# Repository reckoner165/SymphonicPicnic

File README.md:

# SymphonicPicnic
A repo for Teensy and XBee codes for the mushrooms

TEsting : Arduino Teensy Changes for SD optimization
enable : #define USE_TEENSY3_OPTIMIZED_CODE
SD_t3.h : /Applications/<Arduino-App-Folder>/Contents/Java/hardware/teensy/avr/libraries/SD/SD_t3.h

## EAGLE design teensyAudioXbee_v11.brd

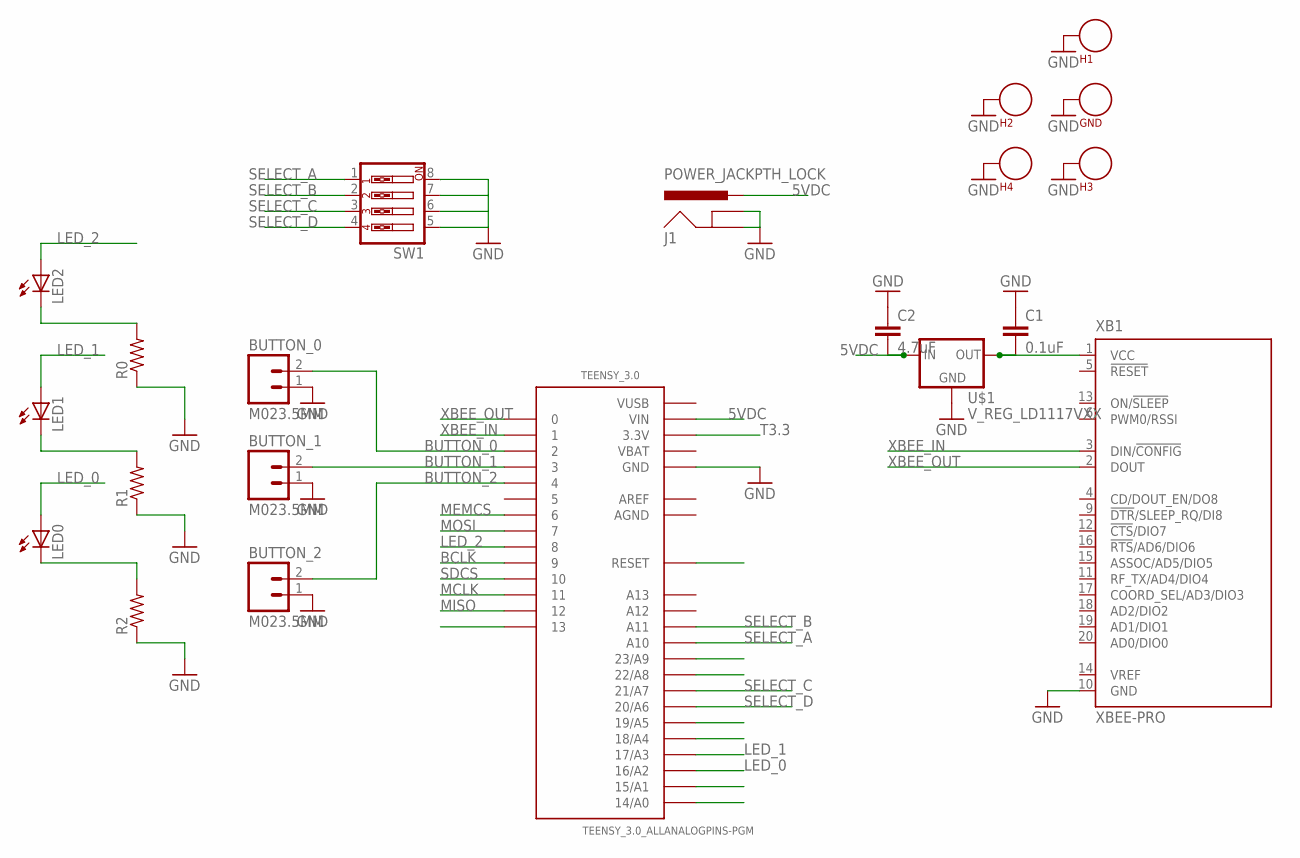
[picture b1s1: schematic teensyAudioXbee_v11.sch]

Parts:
BUTTON_0, BUTTON_1, BUTTON_2: M023.5MM; SCREWTERMINAL-3.5MM-2
C1: 0.1uF; CAP-PTH-SMALLEZ
C2: 4.7uF; CAP-PTH-SMALLEZ
GND: SEW_HOLE; SIMPLE_HOLE
H1, H2, H3, H4: SEW_HOLE; SIMPLE_HOLE
J1: POWER_JACKPTH_LOCK; POWER_JACK_PTH_LOCK
LED0, LED1, LED2: LED_ELD260; LED_LD260
R0, R1, R2: RESISTORPTH-1/6W; 1/6W-RES
SW1: SW_DIP-4; EDG-04
TEENSY_3.0: TEENSY_3.0_ALLANALOGPINS-PGM; TEENSY_3.0_ALLANALOG-PGM
U$1: V_REG_LD1117VXX; 78XXL
XB1: XBEE-PRO

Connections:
3.3VDC: C1.2, U$1.GND (OUT), XB1.1 (VCC)
5VDC: C2.2, J1.PWR, TEENSY_3.0.VIN, U$1.OUT (IN)
AGND: TEENSY_3.0.AGND
AREF: TEENSY_3.0.AREF
BCLK: TEENSY_3.0.9
BUTTON_0: BUTTON_0.2, TEENSY_3.0.2
BUTTON_1: BUTTON_1.2, TEENSY_3.0.3
BUTTON_2: BUTTON_2.2, TEENSY_3.0.4
GND: BUTTON_0.1, BUTTON_1.1, BUTTON_2.1, C1.1, C2.1, GND.P$1, H1.P$1, H2.P$1, H3.P$1, H4.P$1, J1.GND, J1.GNDBREAK, R0.1, R1.1, R2.1, SW1.5, SW1.6, SW1.7, SW1.8, TEENSY_3.0.GND, TEENSY_3.0.GND1 (GND), TEENSY_3.0.GND2 (GND), U$1.IN (GND), XB1.10 (GND)
LED_0: LED0.A, TEENSY_3.0.16/A2
LED_1: LED1.A, TEENSY_3.0.17/A3
LED_2: LED2.A, TEENSY_3.0.8
MCLK: TEENSY_3.0.11
MEMCS: TEENSY_3.0.6
MISO: TEENSY_3.0.12
MOSI: TEENSY_3.0.7
unnamed: LED2.K (C), R0.2
unnamed: LED1.K (C), R1.2
unnamed: LED0.K (C), R2.2
SDCS: TEENSY_3.0.10
SELECT_A: SW1.1, TEENSY_3.0.A10
SELECT_B: SW1.2, TEENSY_3.0.A11
SELECT_C: SW1.3, TEENSY_3.0.21/A7
SELECT_D: SW1.4, TEENSY_3.0.20/A6
T3.3: TEENSY_3.0.3.3V, TEENSY_3.0.3.3V1 (3.3V), TEENSY_3.0.3.3V2 (3.3V)
VBAT: TEENSY_3.0.VBAT
VUSB: TEENSY_3.0.VUSB
XBEE_IN: TEENSY_3.0.1, XB1.3 (DIN/!CONFIG)
XBEE_OUT: TEENSY_3.0.0, XB1.2 (DOUT)

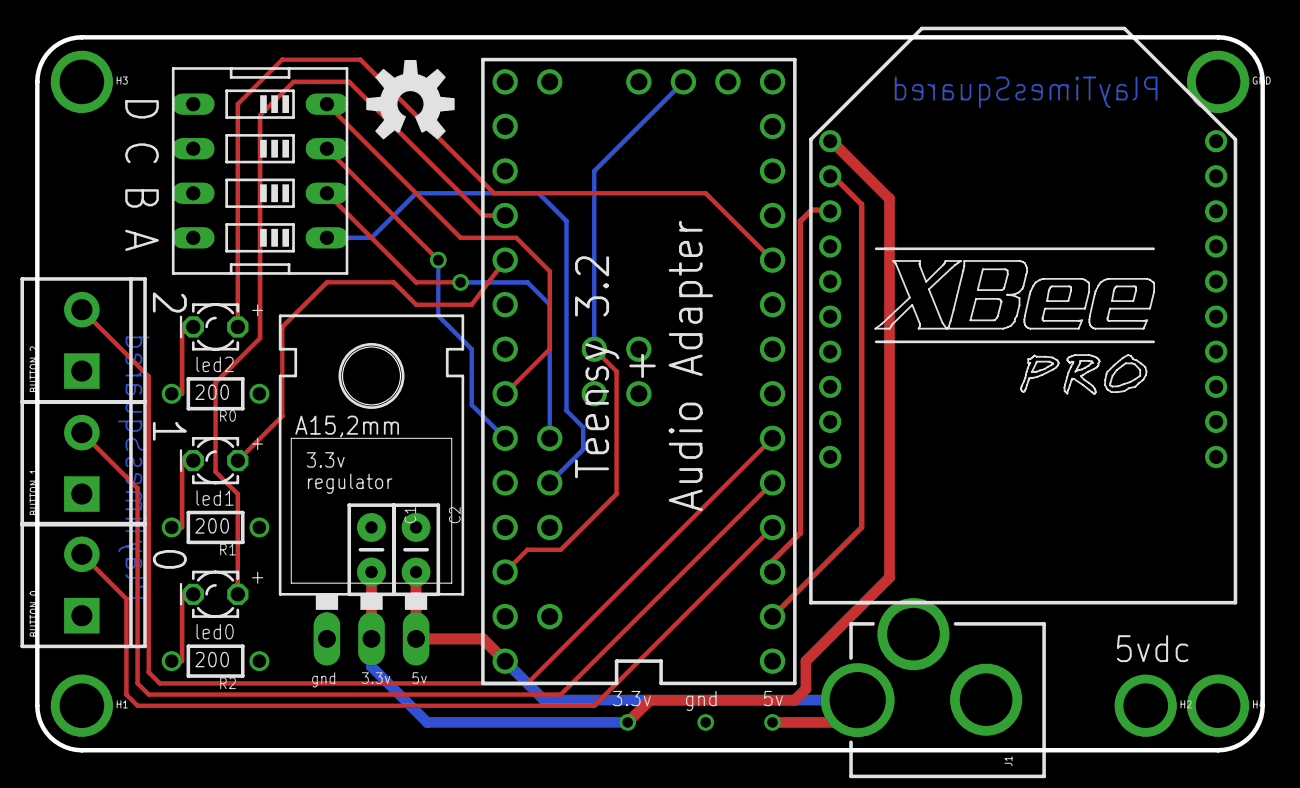
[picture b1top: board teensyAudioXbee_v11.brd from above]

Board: 2 copper layers, 69.9 x 40.6 mm, 22 parts (0 on the bottom side), 19 nets.

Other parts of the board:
U$2: OSHW-LOGO-M

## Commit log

2016-06-22 teensyXbeeAudioShieldCode
2016-06-22 update1
2016-06-22 update2
2016-06-22 added eagle cad files
2016-06-23 v2 has backing track, v3 adds mixers manager but it's not working yet
2016-06-23 folder of sounds
2016-07-04 button test
2016-07-04 changed led setup
2016-07-04 added buttons leds
2016-07-05 switch change
2016-07-05 minor changes
2016-07-05 added other button indicator
2016-07-05 deleted v4
2016-07-05 testing serial priorities
2016-07-06 teesnsy sd test for clicking
2016-07-07 2 channel audio player
2016-07-08 added sketch with sounds stored in memory
2016-07-08 rm extra memory files
2016-07-09 changed baud rate to 57600 and added random delay before sending Serial1 command
2016-07-11 Increased volume and changed audio files
2016-07-12 Added audio files
2016-07-13 added channels

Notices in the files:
parts and their libraries:
SparkFun-Connectors: Licensing: CC v3.0 Share-Alike You are welcome to use this library for commercial purposes.
SparkFun-Passives: Licensing: Creative Commons ShareAlike 4.0 International - https://creativecommons.org/licenses/by-sa/4.0
